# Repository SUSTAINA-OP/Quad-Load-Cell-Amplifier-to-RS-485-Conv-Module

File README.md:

<html lang="en">

<head>
	<meta charset="uft-8">
	<meta name="author" content="Masato Kubotera">
    <meta name="description" content="">
</head>

<body>
    <p><strong>This product is currently under development!</strong></p>
	<h1>Quad Load Cell Amplifier to RS-485 Conv. Module</h1>
        <p>
            This product can connect up to four load cells, and the change in resistance of the load cells can be amplified by an amplifier to 24 bit and sensed by a microcontroller at 80 Hz. This product uses a ready-made microcontroller board, simplifying PCB design and assembly of electronic components. For communication with the microcontroller, in addition to the USB connector on the microcontroller, RS-485 converted from UART  is available.<br>
            The RS-485 I/F connector has power input of up to 15 V. This allows servo motors with RS-485 I/F to be connected to the same bus as servo motors, etc.<br>
            The microcontroller that can be attached to this product is the <a href="https://www.seeedstudio.com/XIAO-c-1964.html?">XIAO series</a> manufactured by Seeed Studio. Select a microcontroller from the lineup according to the required performance.
            <br>
            <br>
            This product is developed as a foot load measurement module for SUSTAINA-OP<sup>TM</sup> and is used, for example, to estimate the position of the robot's center of mass.<br>
            In SUSTAINA-OP<sup>TM</sup>, four of the following load cells are connected to this module.
            <ul>
                <li><a href="https://www.alibaba.com/product-detail/SC700-Fishing-Scales-Small-Size-thin_60710601230.html">SC700-40kg (Sensor and Control Co., Ltd.)</a></li>
            </ul>
            The following microcontrollers are attached to this module.
            <ul>
                <li><a href="https://www.seeedstudio.com/Seeeduino-XIAO-Arduino-Microcontroller-SAMD21-Cortex-M0+-p-4426.html?">XIAO SAMD21 (Seeed Studio)</a></li>
            </ul>     
        </p>
	<h2>Features Rev. 1</h2>
        <p>
            <table>
                <tr>
                    <th>Top Surface of PCB</th>
                    <th>Bottom Surface of PCB</th>
                    <th>Assembled Electronic Components</th>
                </tr>
                <tr>
                    <td></td>
                    <td></td>
                    <td></td>
                </tr>
            </table>
        </p>
    <h3>PCB</h3>
        <p>
            <ul>
                <li>50 mm x 40 mm PCB layout</li>
                <li>4 x ø3.2 Mounting Holes</li>
                <li>
                    4 x Load Cell Ports
                    <ul>
                        <li>1" (2.54mm) pitch through-holes for XH connecter(JST)
                            <ul>
                                <li>BLK/E-: Excitation- (E-) or GND</li>
                                <li>RED/E+: Excitation+ (E+) or VCC</li>
                                <li>GRN/A+: Output+, Signal+, or Amplifier+</li>
                                <li>WHT/A-: Output-, Signal-, or Amplifier-</li>
                            </ul>
                        </li>
                    </ul>
                </li>
                <li>
                    1 x RS-485 I/F Port
                    <ul>
                        <li>1" (2.54mm) pitch through-holes for XH connecter(JST)
                            <ul>
                                <li>DM: RS-485 Data Signal Minus</li>
                                <li>DP: RS-485 Data Signal Plus</li>
                                <li>VCC: Power Input (Input voltage: 6.2~15V)</li>
                                <li>GND: Common Ground</li>
                            </ul>
                        </li>
                    </ul>
                </li>
            </ul>
        </p>
    <h3><a href="http://en.aviaic.com/detail/730856.html">AVIA HX711</a></h3>
        <p>
            <ul>
                <li>Two selectable differential input channels</li>
                <li>On-chip active low noise PGA with selectable gain of 32, 64 and 128</li>
                <li>On-chip power supply regulator for load-cell and ADC analog power supply</li>
                <li>On-chip oscillator requiring no external component with optional external crystal</li>
                <li>On-chip power-on-reset</li>
                <li>Simple digital control and serial interface: pin-driven controls, no programming needed</li>
                <li>Selectable 10SPS or 80SPS output data rate</li>
                <li>Simultaneous 50 and 60Hz supply rejection</li>
                <li>Current consumption including on-chip analog power supply regulator: normal operation < 1.5mA, power down < 1uA</li>
                <li>Operation supply voltage range: 2.6 ~ 5.5V</li>
                <li>Operation temperature range: -40 ~ +85C</li>
                <li>16 pin SOP-16 package</li>
            </ul>
        <p>
	<h2>Development Environments</h2>
    <p>
        This product is designed with the following software.
            <ul>
                <li><a href="https://www.autodesk.com/products/eagle/overview">Autodesk Eagle 9.6.2</a></li>
            </ul>
    </p>
    <h2>Repository Contents</h2>
        <p>
            <dl>
                <dt><a href="/images">\images</a></dt>
                <dd>PCB preview images and capture of design screen</dd>
                <dt><a href="/libraries">\libraries</a></dt>
                <dd>Libraries used in Autodesk Eagle design</dd>
                <dt><a href="/documents">\documents</a> </dt>
                <dd>Documentation for making and using this product</dd>
                <dt><a href="/pcb_order">\pcb_order</a> </dt>
                <dd>Gerber data and documentation for ordering PCB</dd>
                <dt><a href="/schematic.pdf">schematic.pdf</a></dt>
                <dd>Circuit diagram of this product</dd>
                <dt>*.brd</dt>
                <dd>Board wiring design file by Autodesk Eagle</dd>
                <dt>*.sch</dt>
                <dd>Circuit diagram design file by Autodesk Eagle</dd>
                <dt><a href="/.gitignore">.gitignore</a></dt>
                <dd>A file that tells Git not to track a particular file</dd>            <dt><a href="/LICENSE">LICENSE</a></dt>
                <dd>License to use this product</dd>
            </dl>
        </p>
    <h2>Documentation</h2>
        <p>
            The following documents are available for this product.
            <ul>
                <li><a href="/pcb_order/README.md">\pcb_order\README.md</a>: Information for ordering the PCB</li>
                <li><a href="/documents/BOM.md">\document\BOM.md</a>: List of electronic components assembled on the PCB</li>
            </ul>
        </p>
    <h2>References</h2>
        <p>
            This product was designed with reference to the following products.
            <ul>
                <li><a href="https://www.sparkfun.com/products/13879">SparkFun Load Cell Amplifier - HX711</a></li>
            </ul>
        </p>
    <h3>Acknowledgements</h3>
        <p>
            The development of this module is based on the following foot load measurement modules in the RoboCup Humanoid League.
            <ul>
                <li><a href="https://github.com/Rhoban/ForceFoot">Rhoban/ForceFoot</a>: Robotic foot design involving force sensors</li>
                <li><a href="https://github.com/bit-bots/bit_foot">bit-bots/bit_foot</a>: Foot pressure sensor for a humanoid robot</li>
            </ul>
            I would like to take this opportunity to thank you.
        </p>
    <h2>Contact</h2>
        <p>
            If you have any questions, please contact the designer of this product, Masato Kubodera, by <a href="mailto:masato.kubotera@sustaina-op.com">e-mail</a>.<br>
            E-mail: <a href="mailto:masato.kubotera@sustaina-op.com">masato.kubotera@sustaina-op.com</a>
        </p>
    <h2>License Information</h2>
        <p>
            This product is open source. Please review the <a href="/LICENSE">LICENSE</a> for license information.<br>
            <br>
            This product by Masato Kubotera is licensed under a <a href="http://creativecommons.org/licenses/by-nc-sa/4.0/">Creative Commons Attribution-NonCommercial-ShareAlike 4.0 International License</a>.
        </p>    
</body>
</html>

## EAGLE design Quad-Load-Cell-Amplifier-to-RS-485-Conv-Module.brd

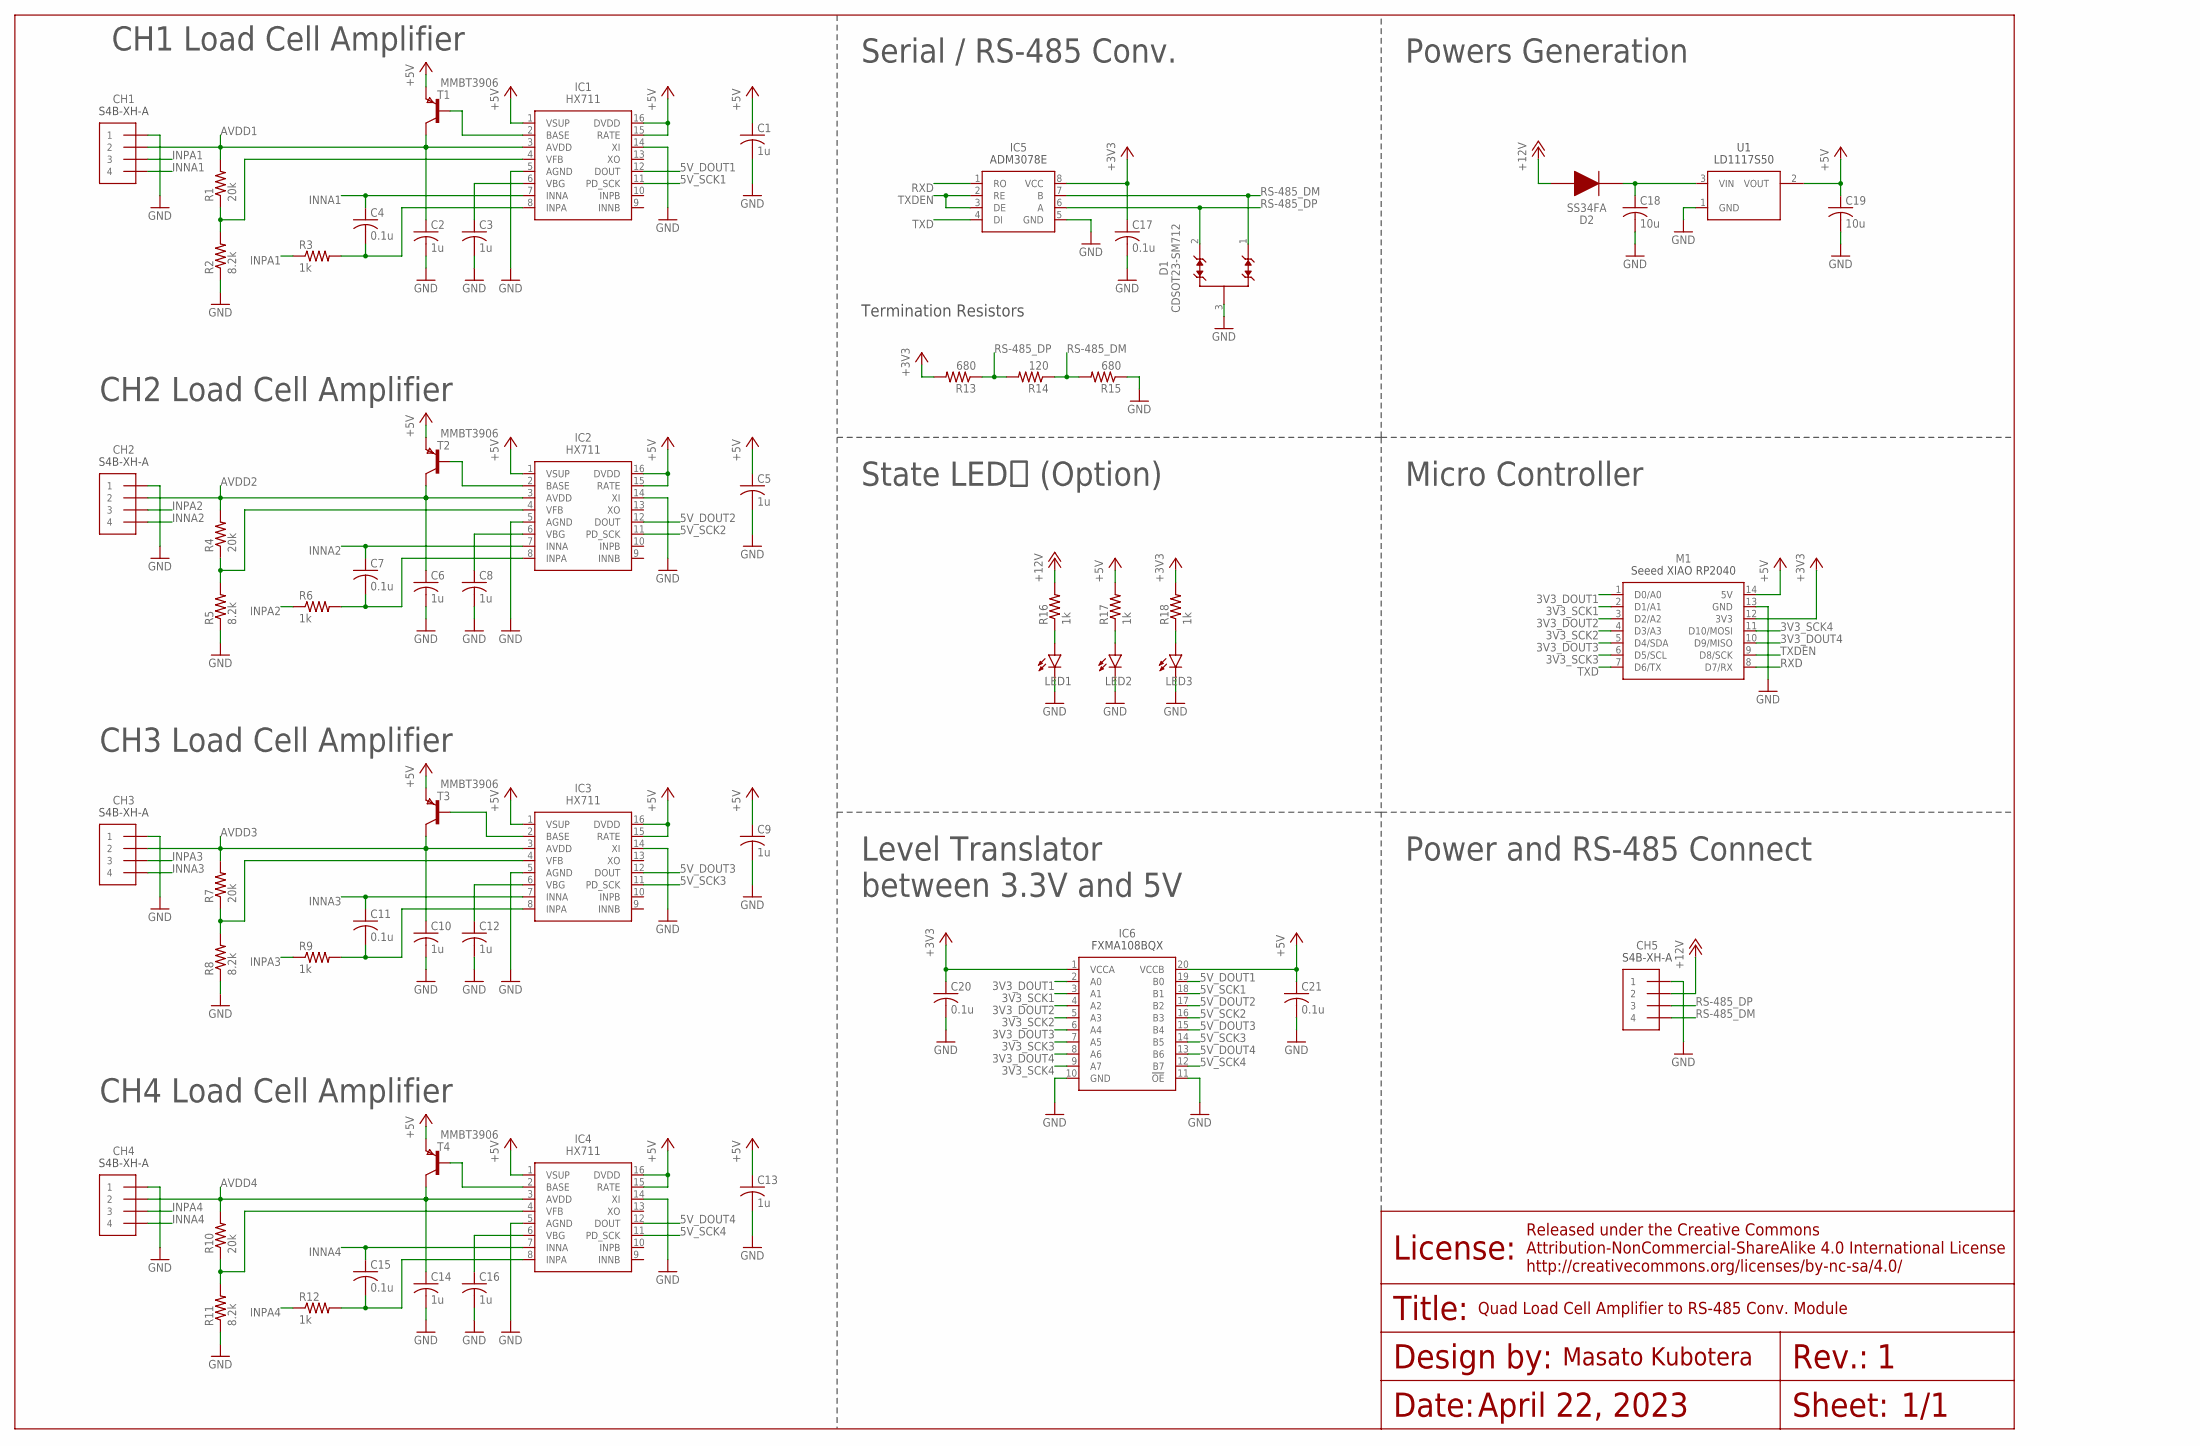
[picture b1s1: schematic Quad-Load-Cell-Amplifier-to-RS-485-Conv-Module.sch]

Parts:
C1, C2, C3, C5, C6, C8, C9, C10, C12, C13, C14, C16: 1u; C0603
C4, C7, C11, C15, C17, C20, C21: 0.1u; C0603
C18, C19: 10u; C0603
CH1, CH2, CH3, CH4, CH5: S4B-XH-A
D1: CDSOT23-SM712; SOT-23-3
D2: SS34FA
IC1, IC2, IC3, IC4: HX711
IC5: ADM3078E
IC6: FXMA108BQX; QFN-20
LED1, LED2, LED3: LEDSML0603; SML0603
M1: SEEED_XIAO_RP2040_HOLE; SEEED_XIAO_HOLE
R1, R4, R7, R10: 20k; R0603
R2, R5, R8, R11: 8.2k; R0603
R3, R6, R9, R12, R16, R17, R18: 1k; R0603
R13, R15: 680; R0603
R14: 120; R0603
T1, T2, T3, T4: MMBT3906; SOT-23
U1: LD1117S50; SOT-223

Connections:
3V3_DOUT1: IC6.2 (A0), M1.1 (D0/A0)
3V3_DOUT2: IC6.4 (A2), M1.3 (D2/A2)
3V3_DOUT3: IC6.6 (A4), M1.5 (D4/SDA)
3V3_DOUT4: IC6.8 (A6), M1.10 (D9/MISO)
3V3_LED: LED3.A, R18.1
3V3_SCK1: IC6.3 (A1), M1.2 (D1/A1)
3V3_SCK2: IC6.5 (A3), M1.4 (D3/A3)
3V3_SCK3: IC6.7 (A5), M1.6 (D5/SCL)
3V3_SCK4: IC6.9 (A7), M1.11 (D10/MOSI)
5V_DOUT1: IC1.12 (DOUT), IC6.19 (B0)
5V_DOUT2: IC2.12 (DOUT), IC6.17 (B2)
5V_DOUT3: IC3.12 (DOUT), IC6.15 (B4)
5V_DOUT4: IC4.12 (DOUT), IC6.13 (B6)
5V_LED: LED2.A, R17.1
5V_SCK1: IC1.11 (PD_SCK), IC6.18 (B1)
5V_SCK2: IC2.11 (PD_SCK), IC6.16 (B3)
5V_SCK3: IC3.11 (PD_SCK), IC6.14 (B5)
5V_SCK4: IC4.11 (PD_SCK), IC6.12 (B7)
12V_LED: LED1.A, R16.1
+3V3: C17.1, C20.1, IC5.8 (VCC), IC6.1 (VCCA), M1.12 (3V3), R13.2, R18.2
+5V: C1.1, C5.1, C9.1, C13.1, C19.1, C21.1, IC1.1 (VSUP), IC1.15 (RATE), IC1.16 (DVDD), IC2.1 (VSUP), IC2.15 (RATE), IC2.16 (DVDD), IC3.1 (VSUP), IC3.15 (RATE), IC3.16 (DVDD), IC4.1 (VSUP), IC4.15 (RATE), IC4.16 (DVDD), IC6.20 (VCCB), M1.14 (5V), R17.2, T1.2 (E), T2.2 (E), T3.2 (E), T4.2 (E), U1.2 (VOUT)
+12V: CH5.2, D2.2, R16.2
AVDD1: C2.1, CH1.2, IC1.3 (AVDD), R1.2, T1.1 (C)
AVDD2: C6.1, CH2.2, IC2.3 (AVDD), R4.2, T2.1 (C)
AVDD3: C10.1, CH3.2, IC3.3 (AVDD), R7.2, T3.1 (C)
AVDD4: C14.1, CH4.2, IC4.3 (AVDD), R10.2, T4.1 (C)
BASE1: IC1.2 (BASE), T1.3 (B)
BASE2: IC2.2 (BASE), T2.3 (B)
BASE3: IC3.2 (BASE), T3.3 (B)
BASE4: IC4.2 (BASE), T4.3 (B)
GND: C1.2, C2.2, C3.2, C5.2, C6.2, C8.2, C9.2, C10.2, C12.2, C13.2, C14.2, C16.2, C17.2, C18.2, C19.2, C20.2, C21.2, CH1.1, CH2.1, CH3.1, CH4.1, CH5.1, D1.3, IC1.5 (AGND), IC1.14 (XI), IC2.5 (AGND), IC2.14 (XI), IC3.5 (AGND), IC3.14 (XI), IC4.5 (AGND), IC4.14 (XI), IC5.5 (GND), IC6.10 (GND), IC6.11 (!OE), LED1.C, LED2.C, LED3.C, M1.13 (GND), R2.1, R5.1, R8.1, R11.1, R15.1, U1.1 (GND)
INNA1: C4.1, CH1.4, IC1.7 (INNA)
INNA2: C7.1, CH2.4, IC2.7 (INNA)
INNA3: C11.1, CH3.4, IC3.7 (INNA)
INNA4: C15.1, CH4.4, IC4.7 (INNA)
INPA1: CH1.3, R3.1
INPA1_: C4.2, IC1.8 (INPA), R3.2
INPA2: CH2.3, R6.1
INPA2_: C7.2, IC2.8 (INPA), R6.2
INPA3: CH3.3, R9.1
INPA3_: C11.2, IC3.8 (INPA), R9.2
INPA4: CH4.3, R12.1
INPA_: C15.2, IC4.8 (INPA), R12.2
RS-485_DM: CH5.4, D1.1, IC5.7 (B), R14.1, R15.2
RS-485_DP: CH5.3, D1.2, IC5.6 (A), R13.1, R14.2
RXD: IC5.1 (RO), M1.8 (D7/RX)
TXD: IC5.4 (DI), M1.7 (D6/TX)
TXDEN: IC5.2 (RE), IC5.3 (DE), M1.9 (D8/SCK)
VBG1: C3.1, IC1.6 (VBG)
VBG2: C8.1, IC2.6 (VBG)
VBG3: C12.1, IC3.6 (VBG)
VBG4: C16.1, IC4.6 (VBG)
VFB1: IC1.4 (VFB), R1.1, R2.2
VFB2: IC2.4 (VFB), R4.1, R5.2
VFB3: IC3.4 (VFB), R7.1, R8.2
VFB4: IC4.4 (VFB), R10.1, R11.2
VIN: C18.1, D2.1, U1.3 (VIN)

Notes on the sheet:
Serial / RS-485 Conv.
Powers Generation
Micro Controller
State LEDｓ (Option)
Power and RS-485 Connect
1/1
April 22, 2023
Quad Load Cell Amplifier to RS-485 Conv. Module
CH1 Load Cell Amplifier
Level Translator between 3.3V and 5V
Termination Resistors
CH2 Load Cell Amplifier
CH3 Load Cell Amplifier
CH4 Load Cell Amplifier

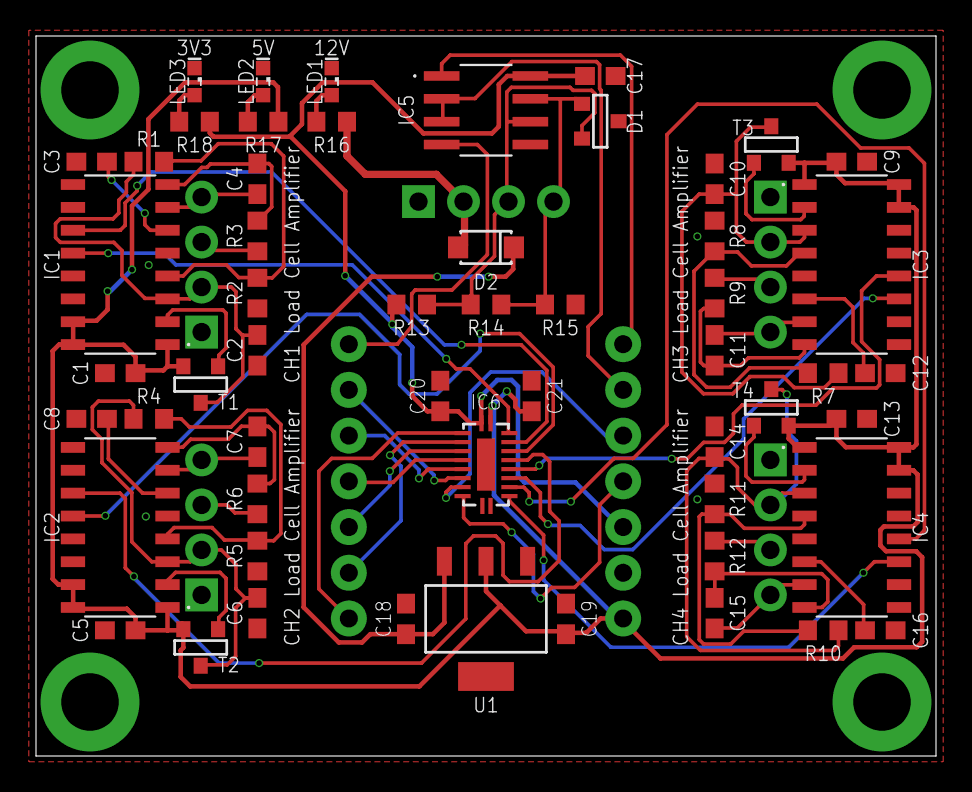
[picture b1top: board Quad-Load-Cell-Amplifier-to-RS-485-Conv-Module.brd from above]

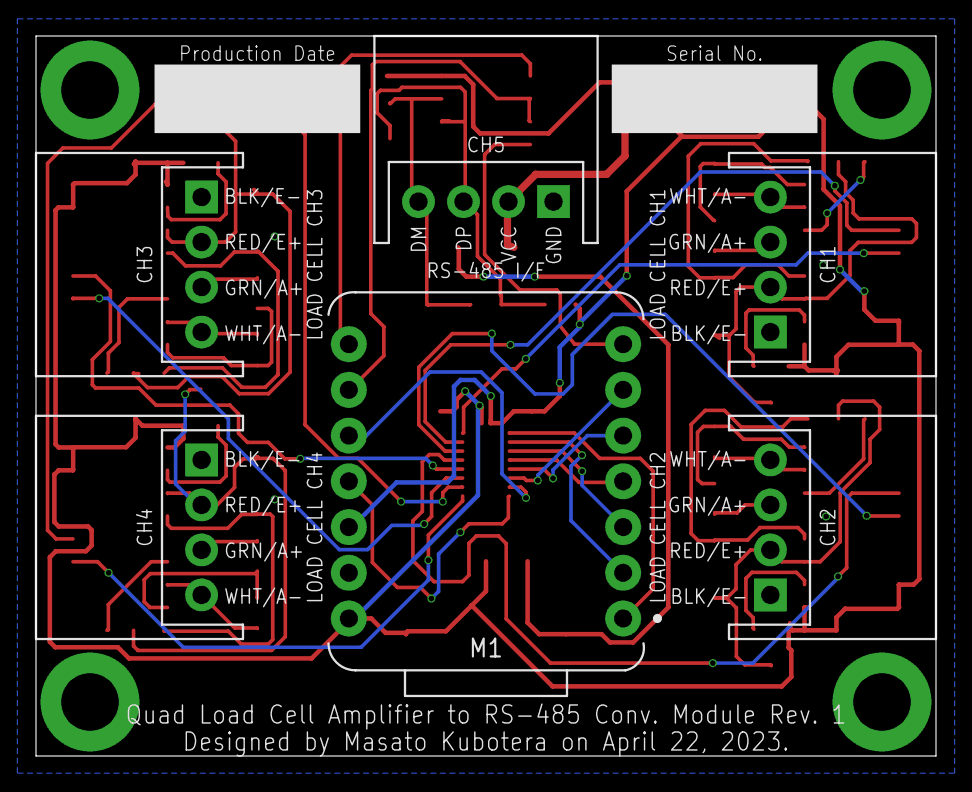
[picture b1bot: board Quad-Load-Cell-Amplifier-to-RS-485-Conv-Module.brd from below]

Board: 2 copper layers, 50.0 x 40.0 mm, 61 parts (6 on the bottom side), 57 nets.

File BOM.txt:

Qty Value                  Device                 Package         Parts                                               Description                
3                          LEDSML0603             SML0603         LED1, LED2, LED3                                    LED                        
7   0.1u                   C-USC0603              C0603           C4, C7, C11, C15, C17, C20, C21                     CAPACITOR, American symbol 
2   10u                    C-USC0603              C0603           C18, C19                                            CAPACITOR, American symbol 
1   120                    R-US_R0603             R0603           R14                                                 RESISTOR, American symbol  
7   1k                     R-US_R0603             R0603           R3, R6, R9, R12, R16, R17, R18                      RESISTOR, American symbol  
12  1u                     C-USC0603              C0603           C1, C2, C3, C5, C6, C8, C9, C10, C12, C13, C14, C16 CAPACITOR, American symbol 
4   20k                    R-US_R0603             R0603           R1, R4, R7, R10                                     RESISTOR, American symbol  
2   680                    R-US_R0603             R0603           R13, R15                                            RESISTOR, American symbol  
4   8.2k                   R-US_R0603             R0603           R2, R5, R8, R11                                     RESISTOR, American symbol  
1   ADM3078E               ADM3078E               ADM3078E        IC5                                                                            
1   CDSOT23-SM712          CDSOT23-SM712          SOT-23-3        D1                                                                             
1   FXMA108BQX             FXMA108BQX             QFN-20          IC6                                                                            
4   HX711                  HX711                  HX711           IC1, IC2, IC3, IC4                                                             
1   LD1117S50              LD1117S50              SOT-223         U1                                                                             
4   MMBT3906               PNPSOT23               SOT-23          T1, T2, T3, T4                                      PNP TRANSISTOR             
5   S4B-XH-A               S4B-XH-A               S4B-XH-A        CH1, CH2, CH3, CH4, CH5                                                        
1   SEEED_XIAO_RP2040_HOLE SEEED_XIAO_RP2040_HOLE SEEED_XIAO_HOLE M1                                                                             
1   SS34FA                 SS34FA                 SS34FA          D2

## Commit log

2023-04-23 Initial Upload
2023-04-27 Rename the folder

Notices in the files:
parts and their libraries:
Frames: Released under the Creative Commons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
